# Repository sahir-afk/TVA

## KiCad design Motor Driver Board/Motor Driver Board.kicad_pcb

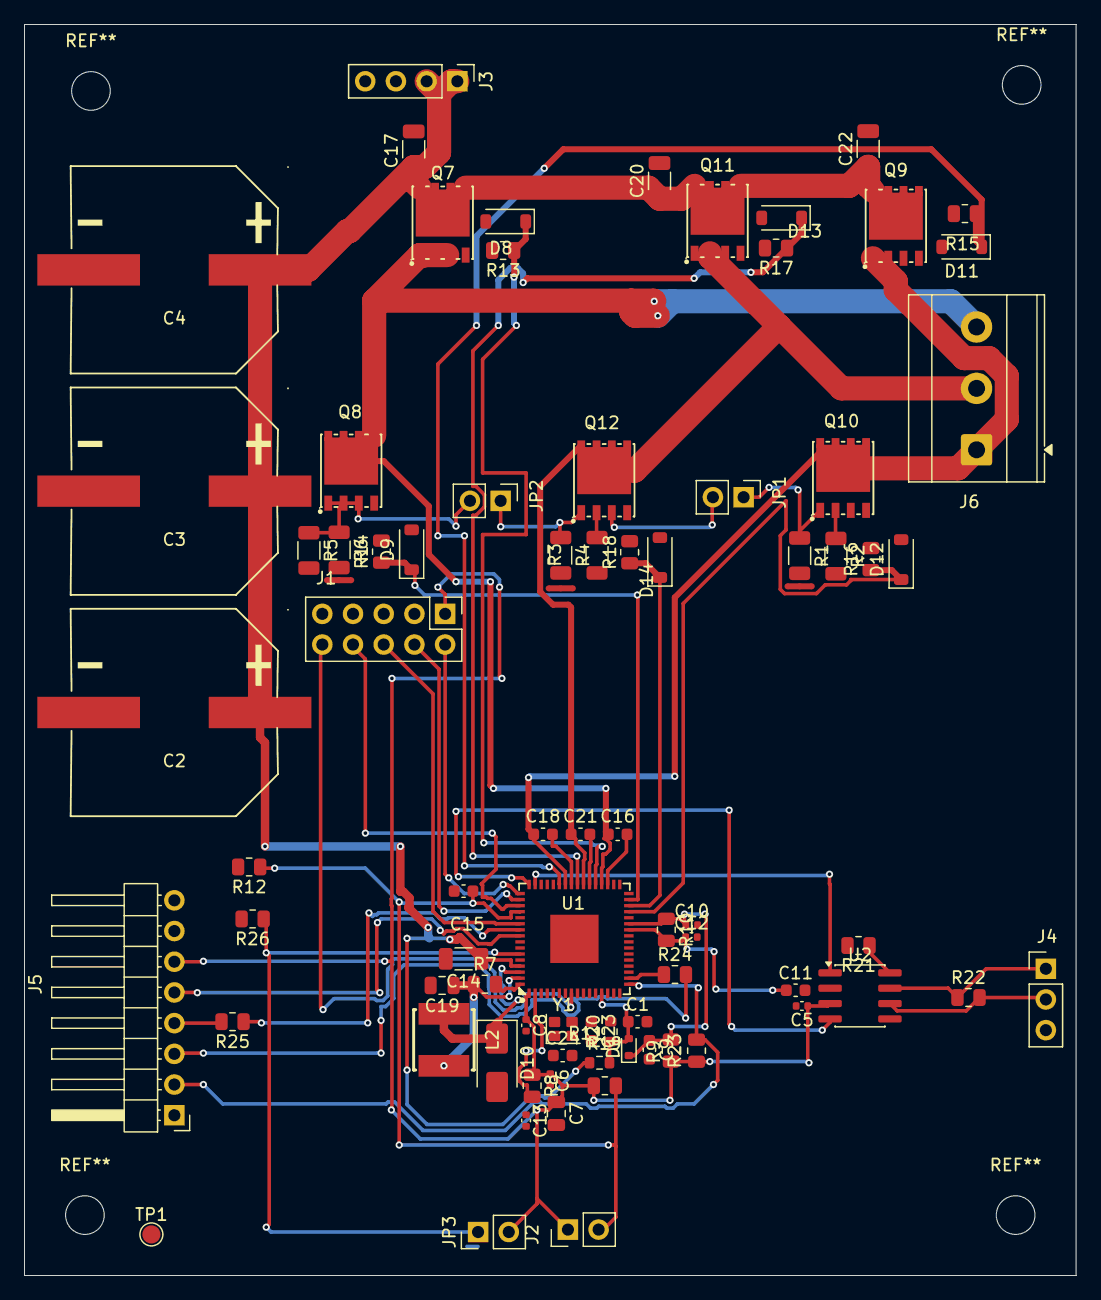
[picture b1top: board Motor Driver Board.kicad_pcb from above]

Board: 4 copper layers, 87.0 x 103.5 mm, 81 parts (0 on the bottom side), 51 nets.

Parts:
C1: 33 nF; C_0603_1608Metric
C2, C3, C4: 220uF 100V; CAP-SMD_BD16.0-L17.0-W17.0-FD
C5, C6: 100nF; C_0402_1005Metric
C7: 10 uF; C_0805_2012Metric
C8, C10, C12, C13: 100 nF; C_0402_1005Metric
C9, C11: 1 uF; C_0603_1608Metric
C14: 220 nF 100V; C_1206_3216Metric
C15: NM; C_0603_1608Metric
C16, C18, C21: 1uF 25V; C_0603_1608Metric
C17, C20, C22: 220nF 100V; C_1206_3216Metric
C19: 10uF 25V; C_0805_2012Metric
C23, C24: 10pF; C_0603_1608Metric
D1: BAT30k; D_SOD-523
D8, D9, D11, D12, D13, D14: BAT48ZFILM; D_SOD-123
D10: STPS1H100A; D_SMA
J1: Conn_02x05_Odd_Even; PinHeader_2x05_P2.54mm_Vertical
J2: Conn_01x02; PinHeader_1x02_P2.54mm_Vertical
J3: Conn_01x04; PinHeader_1x04_P2.54mm_Vertical
J4: Conn_01x03; PinHeader_1x03_P2.54mm_Vertical
J5: Conn_01x08; PinHeader_1x08_P2.54mm_Horizontal
J6: Screw_Terminal_01x03; TerminalBlock_MetzConnect_Type073_RT02603HBLU_1x03_P5.08mm_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
JP1, JP2, JP3: Jumper_2_Open; PinHeader_1x02_P2.54mm_Vertical
L2: 18uH; IND-SMD_L5.0-W5.0_FNR50XXS
NT1, NT2, NT3: NetTie_2; NetTie-3_SMD_Pad0.5mm
Q7, Q8, Q9, Q10, Q11, Q12: Q_NMOS_GDSD; MCAC60N10Y_DFN5060_GDSD
R1, R2, R3, R4, R5, R6: 200m 1% .5W; R_1206_3216Metric
R7, R8, R9, R10, R21: 0; R_0805_2012Metric
R11: 22k 1%; R_0805_2012Metric
R12: 10k 1%; R_0805_2012Metric
R13, R14, R15, R16, R17, R18: 33; R_0805_2012Metric
R19: 75k 1%; R_0603_1608Metric
R20: 3.01k 1%; R_0603_1608Metric
R22: 120; R_0805_2012Metric
R23, R26: 10k; R_0805_2012Metric
R24, R25: 22; R_0805_2012Metric
TP1: TestPoint; TestPoint_Pad_D1.5mm
U1: STSPIN32G4; VFQFPN-64_L9.0-W9.0-P0.50-TL-EP4.0
U2: SN65HVD230; SOIC-8_3.9x4.9mm_P1.27mm
Y1: 24.000MHz; Crystal_SMD_SeikoEpson_FA128-4Pin_2.0x1.6mm

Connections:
/Motor Driver/VSHUNT1P: JP1.1 (A), Q10.3 (S), R1.1, R2.1
/Motor Driver/VSHUNT2P: JP1.2 (B), JP2.1 (A), Q12.3 (S), R3.1, R4.1
/Motor Driver/VSHUNT3P: JP2.2 (B), Q8.3 (S), R5.1, R6.1
/Root/PA0: C1.1, D1.2 (A), R19.2, R20.1, U1.13 (PA0)
/Root/PA13: J1.2, U1.49 (PA13)
/Root/PA14: J1.4, U1.50 (PA14)
/Root/PA15: J1.8, U1.51 (PA15)
/Root/PB3: J1.6, U1.54 (PB3)
/Root/PF0: C24.1, U1.6 (PF0), Y1.1
/Root/PF1: C23.1, U1.7 (PF1), Y1.3
/Root/PG10: J1.10, U1.8 (PG10)
/Root/SCREF: C15.1, J2.2, R11.2, R12.1, U1.52 (SCREF)
/Root/SW: D10.1 (K), L2.1, U1.62 (SW)
BOOT1: C18.1, U1.41 (BOOT1)
BOOT2: C21.1, U1.38 (BOOT2)
BOOT3: C16.1, U1.35 (BOOT3)
GHS1: D11.1 (K), R15.1, U1.43 (GHS1)
GHS2: D13.1 (K), R17.1, U1.40 (GHS2)
GHS3: D8.1 (K), R13.1, U1.37 (GHS3)
GLS1: D12.1 (K), R16.1, U1.29 (GLS1)
GLS2: D14.1 (K), R18.1, U1.30 (GLS2)
GLS3: D9.1 (K), R14.1, U1.31 (GLS3)
GND: C1.2, C2.2, C3.2, C4.2, C5.2, C6.2, C7.2, C8.2, C9.2, C10.2, C11.2, C12.2, C13.2, C14.2, C15.2, C17.2, C19.2, C20.2, C22.2, C23.2, C24.2, D10.2 (A), J1.3, J1.5, J1.9, J3.3, J3.4, J4.3, J5.1, J5.7, J5.8, NT1.2, NT2.2, NT3.2, R1.2, R2.2, R3.2, R4.2, R5.2, R6.2, R12.2, R20.2, R21.2, R26.2, TP1.1 (1_1), U1.32 (PGND), U1.65 (VSS), U2.2 (GND), Y1.2 (G), Y1.4 (G)
unnamed: D8.2 (A), Q7.1 (G), R13.2
unnamed: D9.2 (A), Q8.1 (G), R14.2
unnamed: D11.2 (A), Q9.1 (G), R15.2
unnamed: D12.2 (A), Q10.1 (G), R16.2
unnamed: D13.2 (A), Q11.1 (G), R17.2
unnamed: D14.2 (A), Q12.1 (G), R18.2
unnamed: J4.1, R22.1, U2.7 (CANH)
unnamed: J4.2, R22.2, U2.6 (CANL)
unnamed: J5.3, R24.2
unnamed: J5.4, R25.2
unnamed: JP3.1 (A), R26.1, U1.59 (PB8)
unnamed: R21.1, U2.8 (Rs)
OUT1: C18.2, J6.1, Q9.3 (S), Q10.2 (D), Q10.4 (D), U1.42 (OUT1)
OUT2: C21.2, J6.2, Q11.3 (S), Q12.2 (D), Q12.4 (D), U1.39 (OUT2)
OUT3: C16.2, J6.3, Q7.3 (S), Q8.2 (D), Q8.4 (D), U1.36 (OUT3)
PA4: J5.2, R23.2, U1.17 (PA4)
PA5: R24.1, U1.18 (PA5)
PA11: U1.48 (PA12), U2.4 (R)
PA12: U1.47 (PA11), U2.1 (D)
PB4: J5.5, U1.56 (PB5)
PB5: R25.1, U1.55 (PB4)
VBAT: C13.1, R8.2, U1.2 (VBAT)
VCC: C19.1, L2.2, R7.1, U1.63 (VCC)
VDD: C5.1, C6.1, C7.1, C8.1, J1.1, J2.1, J5.6, JP3.2 (B), R8.1, R9.1, R11.1, R23.1, U1.1 (REG3V3/VDD), U2.3 (VCC)
VDDA: C9.1, C10.1, D1.1 (K), R9.2, R10.1, U1.27 (VDDA)
VM: C2.1, C3.1, C4.1, C14.1, C17.1, C20.1, C22.1, J3.1, J3.2, Q7.2 (D), Q7.4 (D), Q9.2 (D), Q9.4 (D), Q11.2 (D), Q11.4 (D), R19.1, U1.61 (VM)
VREF+: C11.1, C12.1, R10.2, U1.26 (VREF+)
VREGIN: R7.2, U1.64 (REGIN)
